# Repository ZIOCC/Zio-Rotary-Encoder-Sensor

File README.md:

# Zio Rotary Encoder Sensor

> This product can be available for purchase [here](https://www.smart-prototyping.com/Zio-Rotary-Encoder-Sensor).

#### Description

This is a U-Shaped infrared sensor that can be used to detect the rotational speed of a motor mounted on a robot. This reading can be used to adjust the motor speed if it is too fast or too slow, and to calculate the robot’s real-world travel speed. Using a pair of these sensors, we can also measure the robot’s rotation, enabling navigation based on dead-reckoning methods.

#### Specification

* U-Shaped Sensor Gap: 5mm
* Output Signal Explaination: when the IR beam is unobstructed (not blocked by the encoder disc) it outputs a logic-LOW level(0); when blocked it outputs HIGH Level(1).
* IR Signal Trigger: SN74LVC1G14 Single Schmitt-Trigger Inverter
* Dimension: 32x 14mm
* Weight: 1.9g

#### Links

* [Eagle file](https://github.com/ZIOCC/Zio-Rotary-Encoder-Sensor/)
* [How IR Sensor Works](https://www.digikey.com/en/articles/techzone/2012/feb/using-infrared-technology-for-sensing)
* [SN74LVC1G14 Datasheet](http://www.ti.com/lit/ds/symlink/sn74lvc1g14.pdf)

> ###### About Zio
> Zio is a new line of open sourced, compact, and grid layout boards, fully integrated for Arduino and Qwiic ecosystem. Designed ideally for wearables, robotics, small-space limitations or other on the go projects. Check out other awesome Zio products [here](https://www.smart-prototyping.com/Zio).

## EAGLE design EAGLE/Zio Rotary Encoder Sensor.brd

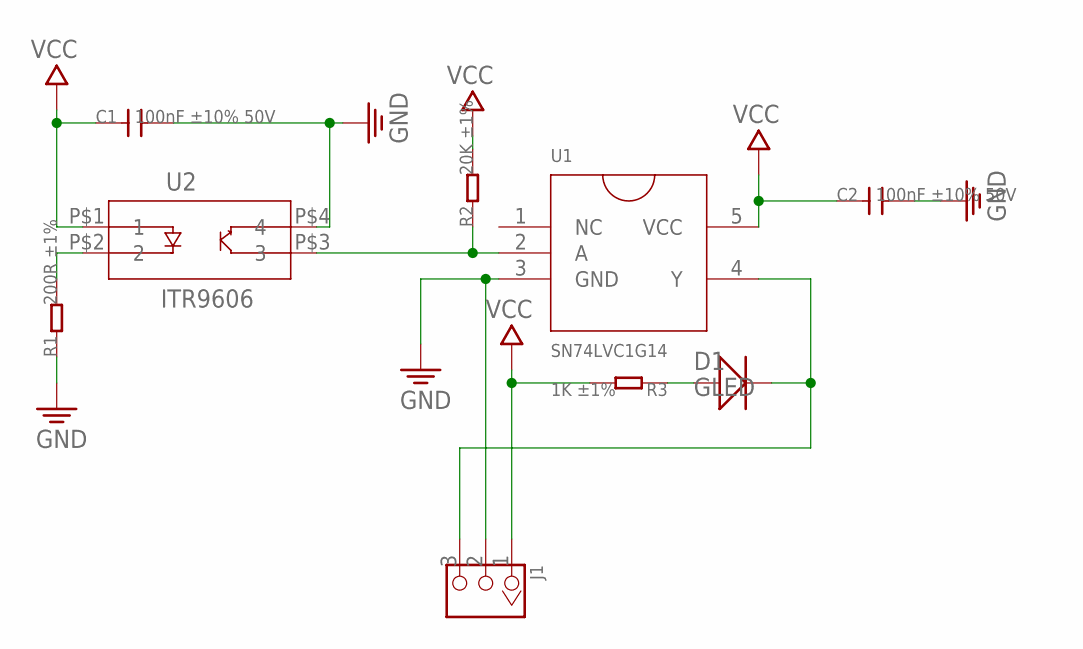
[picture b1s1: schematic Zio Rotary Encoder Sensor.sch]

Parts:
C1, C2: 100nF ±10% 50V; 0603
D1: GLED; SOD523
J1: HEADER-3P-2.54; 3P-2.54
R1: 200R ±1%; 0603
R2: 20K ±1%; 0603
R3: 1K ±1%; 0603
U1: SN74LVC1G14; SOT23-5
U2: ITR9606

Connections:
GND: C1.2, C2.2, J1.2, R1.1, U1.3 (GND), U2.P$4 (4)
unnamed: R1.2, U2.P$2 (2)
unnamed: R2.1, U1.2 (A), U2.P$3 (3)
unnamed: D1.+, R3.1
unnamed: D1.-, J1.3, U1.4 (Y)
VCC: C1.1, C2.1, J1.1, R2.2, R3.2, U1.5 (VCC), U2.P$1 (1)

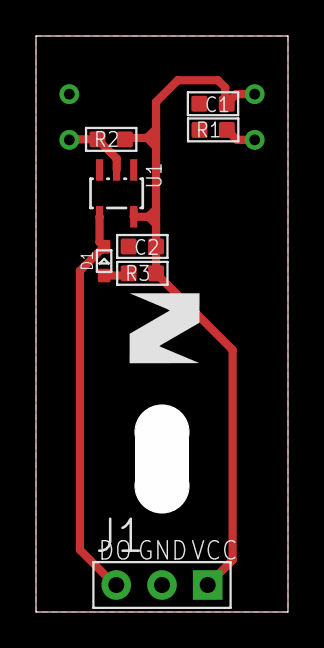
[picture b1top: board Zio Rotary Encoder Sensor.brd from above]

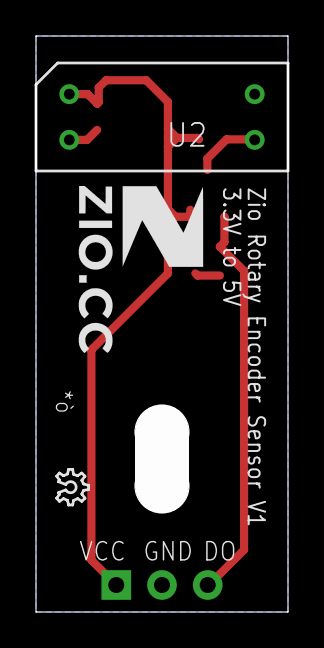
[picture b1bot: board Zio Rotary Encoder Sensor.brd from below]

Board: 2 copper layers, 14.0 x 32.0 mm, 12 parts (3 on the bottom side), 6 nets.

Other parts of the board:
U$5: 6MM
U$6: 7MM
U$7: OSHW_6X70_NOTEXT
